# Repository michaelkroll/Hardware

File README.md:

# Hardware

This repository contains new designs which are not released using the MiKro-Labs brand e.g. new prototypes or designs wich are developed together with other developers/designers.

## BTStack LE Arduino Shield

The BTStack LE Arduino Shield was developed in partnership with the BlueKitchen GmbH. The shield is available from Seeedstudio: http://www.seeedstudio.com/depot/BTstack-LE-Arduino-Shield-p-2464.html and the Arduino Library is available at http://bluekitchen-gmbh.com/btstack-arduino/

Since the design is made available open source, the hardware design files can be downloaded from the BTstackLEArduinoShield/eagle directory.

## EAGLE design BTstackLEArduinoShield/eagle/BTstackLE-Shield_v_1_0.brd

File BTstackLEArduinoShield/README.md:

## BTStack LE Arduino Shield

The BTStack LE Arduino Shield was developed in partnership with the BlueKitchen GmbH (@mringwal). 
The shield is available from Seeedstudio: http://www.seeedstudio.com/depot/BTstack-LE-Arduino-Shield-p-2464.html 
and the Arduino Library is available at http://bluekitchen-gmbh.com/btstack-arduino/ which is needed to run the BTstack ported to 
the Arduino platform.

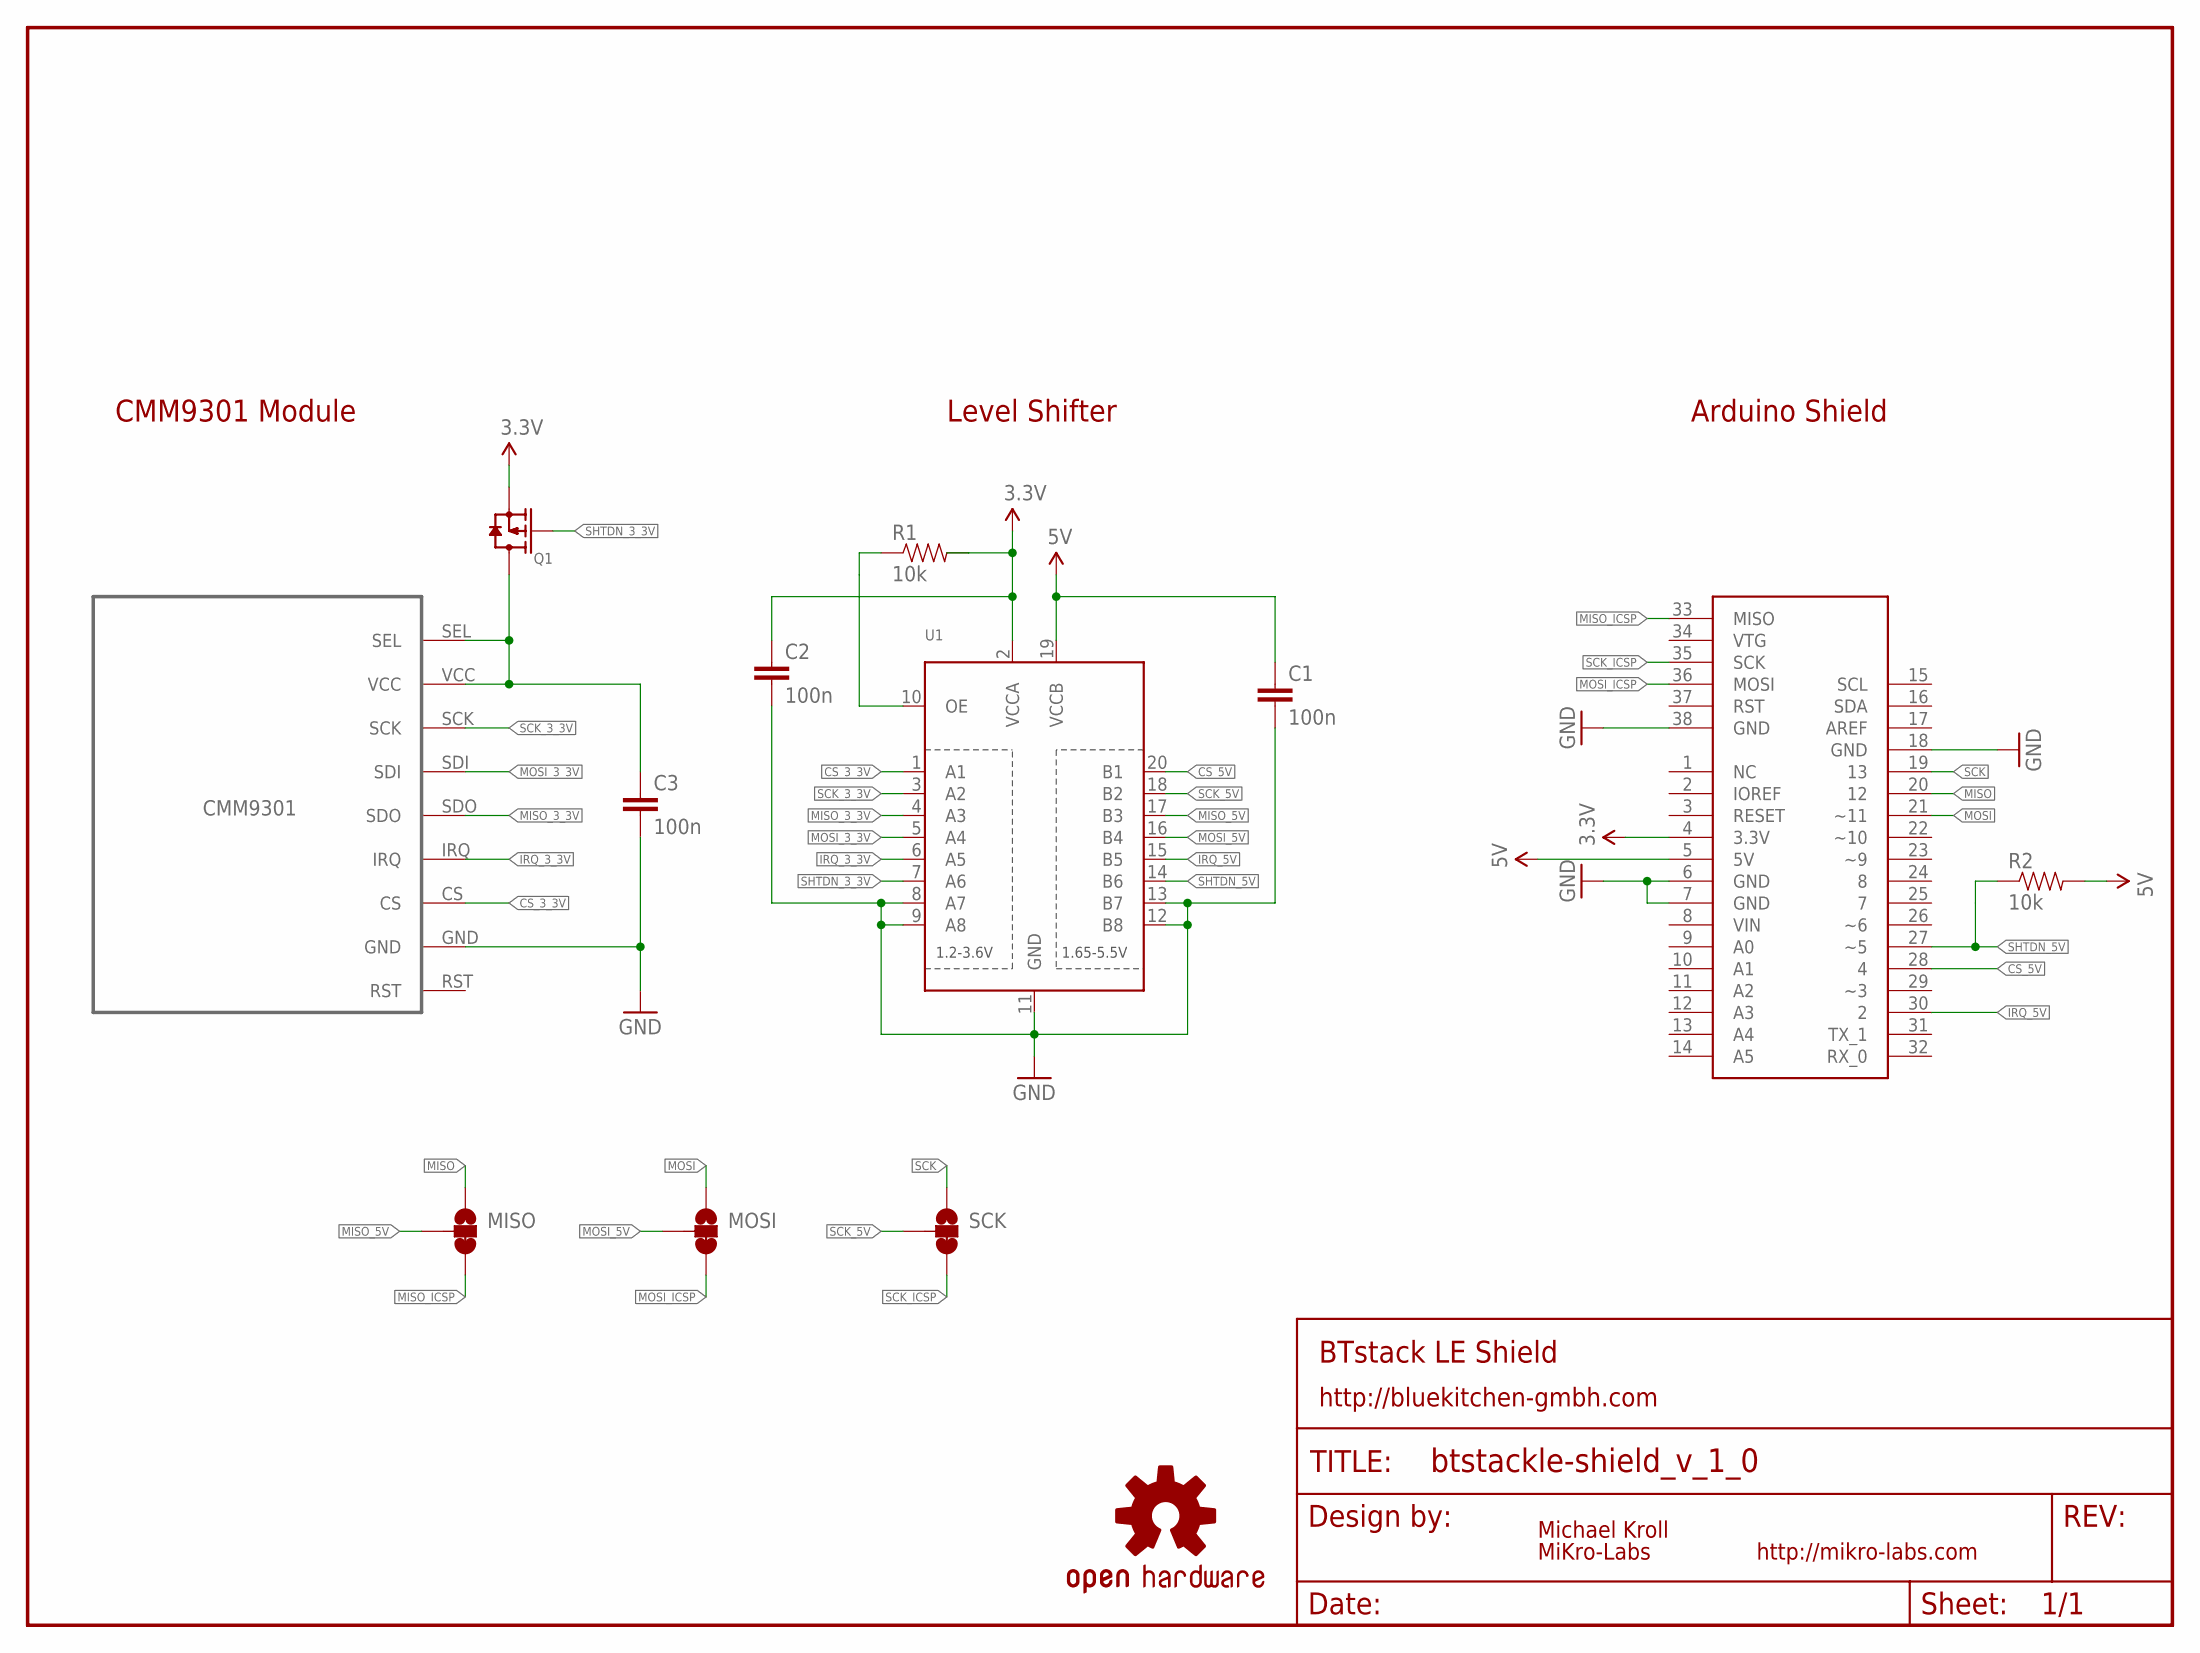
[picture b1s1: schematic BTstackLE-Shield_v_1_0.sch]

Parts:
C1, C2, C3: 100n; 0603-CAP
FRAME1: FRAME-LETTER; CREATIVE_COMMONS
LOGO1: OSHW-LOGOL; OSHW-LOGO-L
MISO: JUMPER-PAD-3-2OF3_NC_BY_TRACE_SMALL; PAD-JUMPER-3-2OF3_NC_BY_TRACE_YES_SILK_FULL_BOX
MOSI: JUMPER-PAD-3-2OF3_NC_BY_TRACE_SMALL; PAD-JUMPER-3-2OF3_NC_BY_TRACE_YES_SILK_FULL_BOX
Q1: MOSFET-P-0440210P1; SOT23
R1, R2: 10k; 0603-RES
SCK: JUMPER-PAD-3-2OF3_NC_BY_TRACE_SMALL; PAD-JUMPER-3-2OF3_NC_BY_TRACE_YES_SILK_FULL_BOX
U1: TXB0108PWR; TSSOP20
U$1: ARDUINO_UNO_SHIELD_ICSP_PADS_ONLY; ICSP_PADS_ONLY
U$4: CMM9301

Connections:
3.3V: C2.1, Q1.2 (S), R1.2, U1.2 (VCCA), U$1.4 (3.3V)
5V: C1.1, R2.2, U1.19 (VCCB), U$1.5 (5V)
CS_3_3V: U1.1 (A1), U$4.CS
CS_5V: U1.20 (B1), U$1.28 (4)
GND: C1.2, C2.2, C3.2, U1.8 (A7), U1.9 (A8), U1.11 (GND), U1.12 (B8), U1.13 (B7), U$1.6 (GND), U$1.7 (GND), U$1.18 (GND), U$1.38 (GND), U$4.GND
IRQ_3_3V: U1.6 (A5), U$4.IRQ
IRQ_5V: U1.15 (B5), U$1.30 (2)
MISO: MISO.1, U$1.20 (12)
MISO_3_3V: U1.4 (A3), U$4.SDO
MISO_5V: MISO.2, U1.17 (B3)
MISO_ICSP: MISO.3, U$1.33 (MISO)
MOSI: MOSI.1, U$1.21 (~11)
MOSI_3_3V: U1.5 (A4), U$4.SDI
MOSI_5V: MOSI.2, U1.16 (B4)
MOSI_ICSP: MOSI.3, U$1.36 (MOSI)
unnamed: C3.1, Q1.3 (D), U$4.SEL, U$4.VCC
unnamed: R1.1, U1.10 (OE)
SCK: SCK.1, U$1.19 (13)
SCK_3_3V: U1.3 (A2), U$4.SCK
SCK_5V: SCK.2, U1.18 (B2)
SCK_ICSP: SCK.3, U$1.35 (SCK)
SHTDN_3_3V: Q1.1 (G), U1.7 (A6)
SHTDN_5V: R2.1, U1.14 (B6), U$1.27 (~5)

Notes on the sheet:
BTstack LE Shield
CMM9301 Module
Level Shifter
Arduino Shield
http://bluekitchen-gmbh.com
http://mikro-labs.com
Michael Kroll
MiKro-Labs

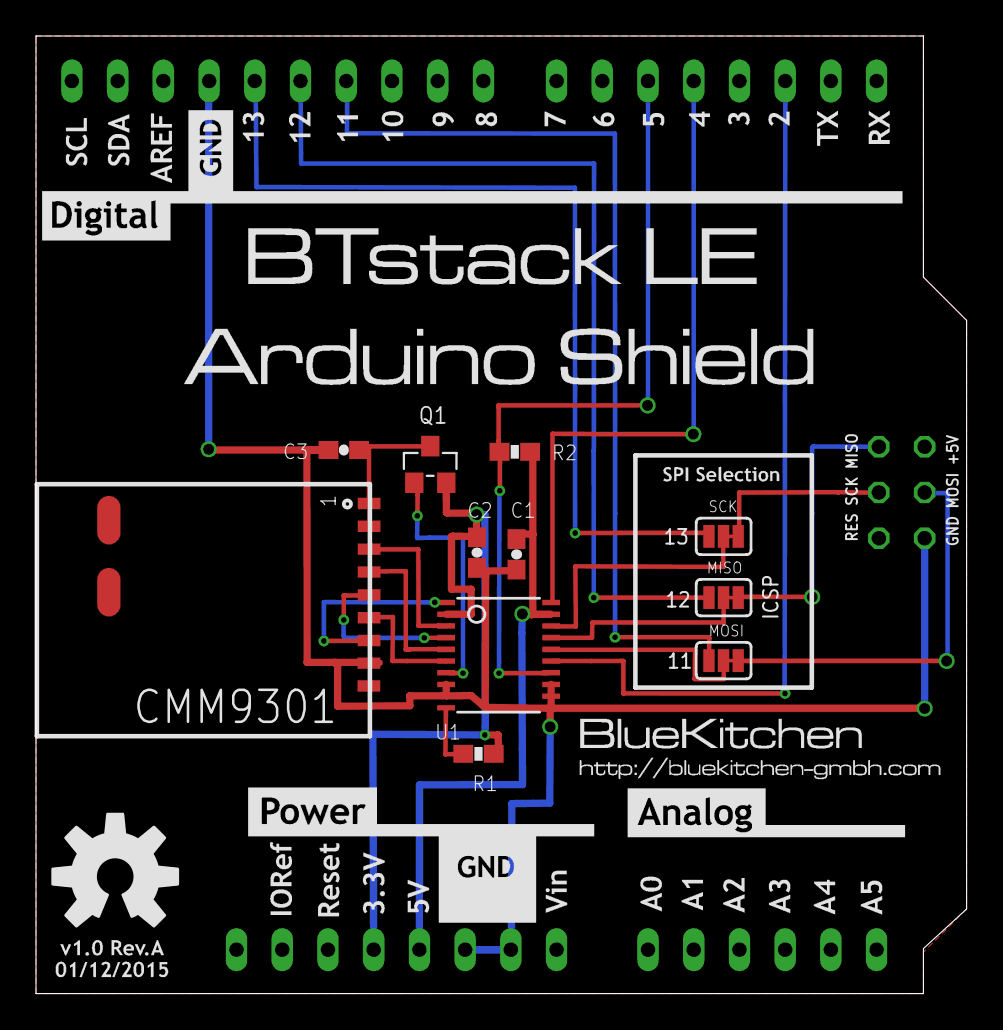
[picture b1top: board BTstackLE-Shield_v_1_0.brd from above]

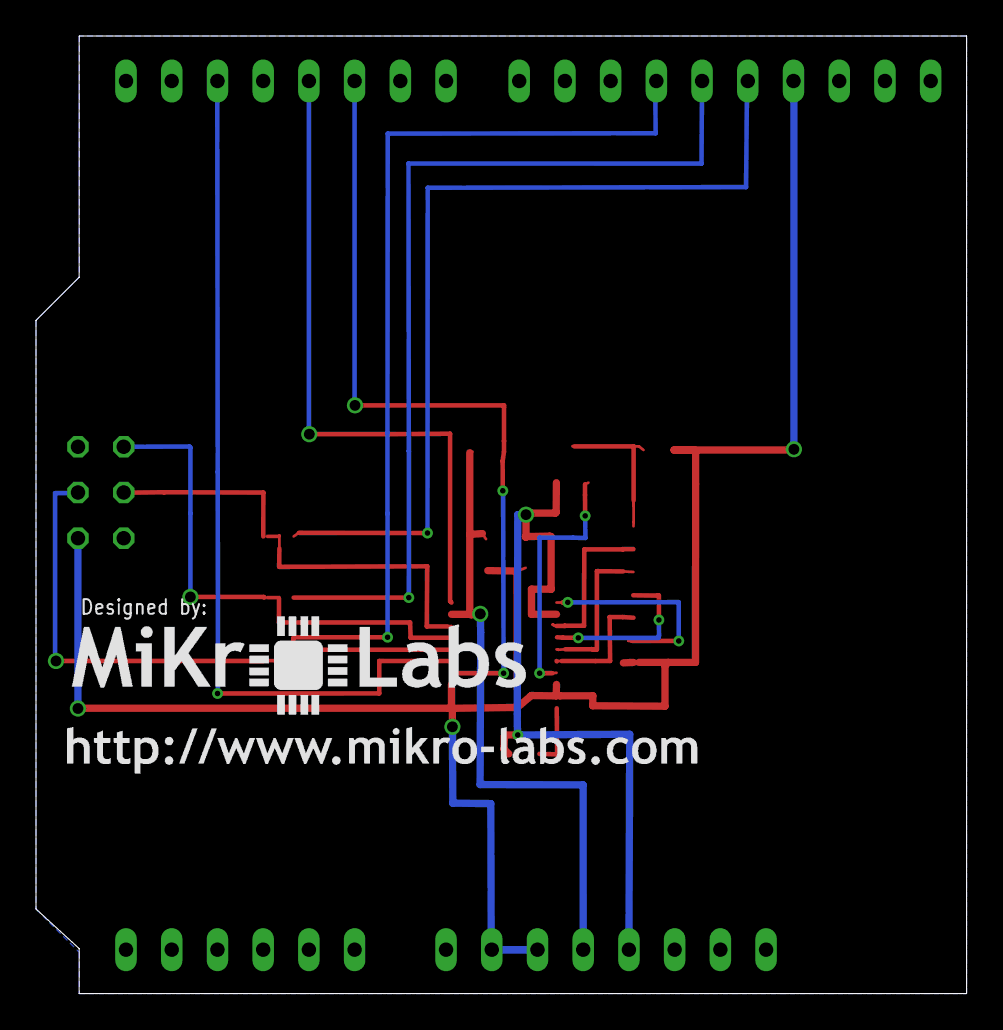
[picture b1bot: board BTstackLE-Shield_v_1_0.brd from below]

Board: 4 copper layers, 51.7 x 53.2 mm, 23 parts (2 on the bottom side), 23 nets.

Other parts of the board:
U$2: DIGITAL
U$3: POWER-ANALOG
U$5: BLUE-KITCHEN-LOGO
U$6: SPI-SELECTION
U$7: BTSTACK-LE-SHIELD-TEXT
U$8: BLUEKITCHEN-LINK
U$9: MIKROLABS-LOGO
U$10: MIKROLABS-URL
U$11: V1_0_01_12_2015

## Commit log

2015-11-15 Update README.md
    Added the initial description for the BTstack LE Arduino Shield.
2015-11-15 Added the BTstack LE Arduino Shield eagle board files.
2015-11-15 Added an illustration to the readme page
2015-11-16 pdf file containing the schematic added.

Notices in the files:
parts and their libraries:
SparkFun-Aesthetics: Licensing: CC v3.0 Share-Alike You are welcome to use this library for commercial purposes.
SparkFun-Passives: Licensing: Creative Commons ShareAlike 4.0 International - https://creativecommons.org/licenses/by-sa/4.0
